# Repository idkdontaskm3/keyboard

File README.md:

# keyboard project!!
### do note - the 75 keyboard is the main project<br>
### the rest is just me learning kicad.
This is just a repo full of my poor attempts at making a keyboard<br>

ive made a very small macro board thingy, alongside a small numpad thing<br>

The 75keyboard pcb is almost complete - I am going to redo some traces<br>
before its done, then start on the case for the keyboard in onshape.<br>

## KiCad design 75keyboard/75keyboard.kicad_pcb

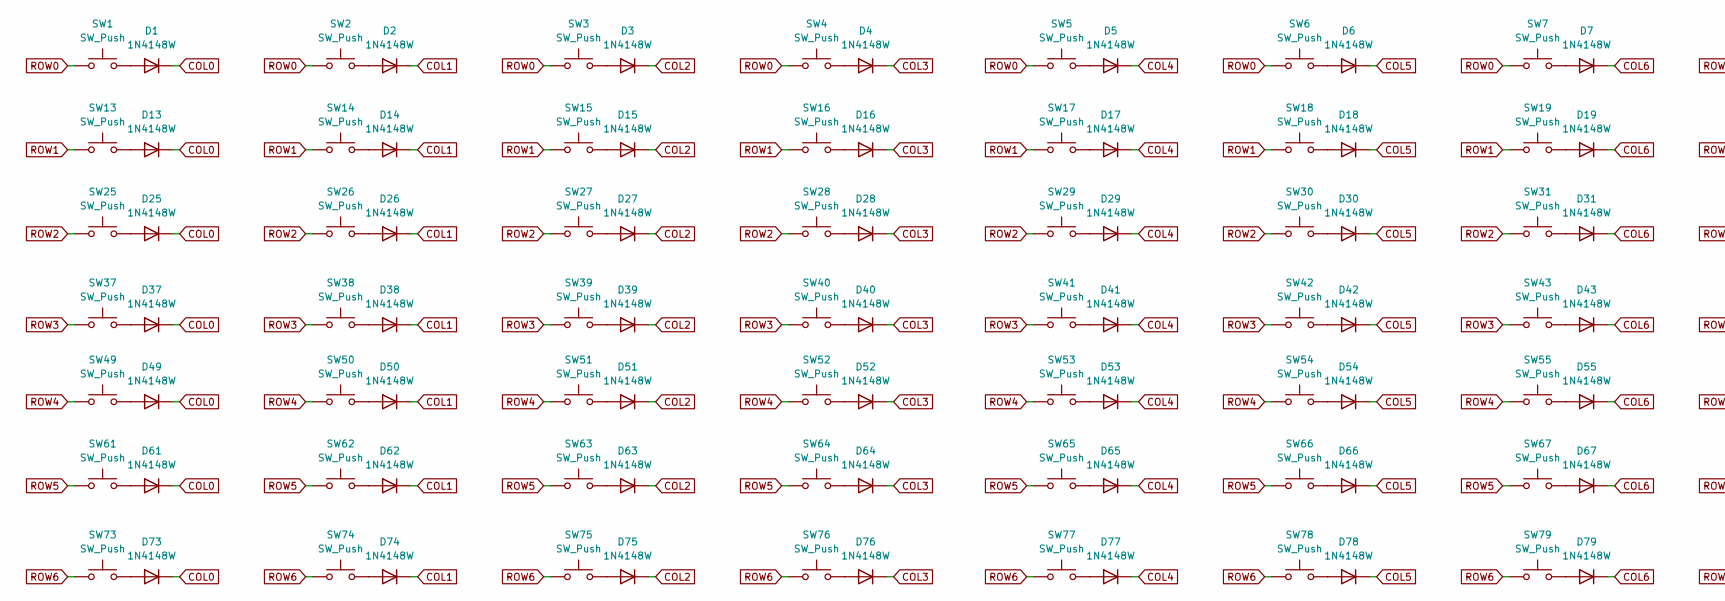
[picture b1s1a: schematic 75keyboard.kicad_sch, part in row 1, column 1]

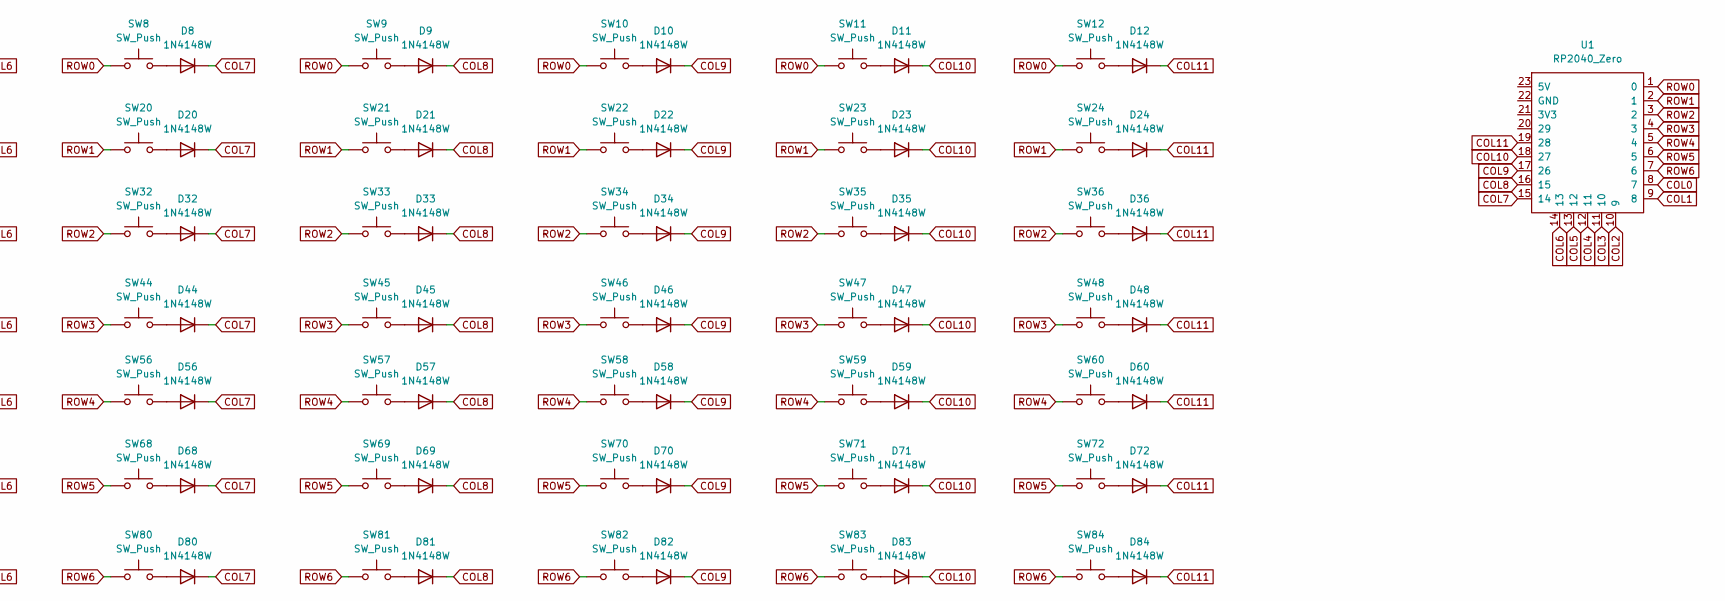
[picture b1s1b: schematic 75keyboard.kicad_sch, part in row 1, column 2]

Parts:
D1, D2, D3, D4, D5, D6, D7, D8, D9, D10, D11, D12, D13, D14, D15, D16, D17, D18, D19, D20, D21, D22, D23, D24, D25, D26, D27, D28, D29, D30, D31, D32, D33, D34, D35, D36, D37, D38, D39, D40, D41, D42, D43, D44, D45, D46, D47, D48, D49, D50, D51, D52, D53, D54, D55, D56, D57, D58, D59, D60, D61, D62, D63, D64, D65, D66, D67, D68, D69, D70, D71, D72, D73, D74, D75, D76, D77, D78, D79, D80, D81, D82, D83, D84: 1N4148W; D_SOD-123
SW1, SW2, SW3, SW4, SW5, SW6, SW7, SW8, SW9, SW10, SW11, SW12, SW13, SW14, SW15, SW16, SW17, SW18, SW19, SW20, SW21, SW22, SW23, SW24, SW25, SW26, SW27, SW28, SW29, SW31, SW33, SW34, SW35, SW36, SW37, SW38, SW39, SW40, SW41, SW42, SW43, SW44, SW46, SW48, SW49, SW50, SW51, SW52, SW53, SW54, SW55, SW56, SW57, SW58, SW60, SW62, SW63, SW64, SW65, SW66, SW67, SW68, SW69, SW70, SW71, SW73, SW74, SW79, SW80, SW81, SW82, SW83, SW84: SW_Push; MX-Solderable-1U
SW30: SW_Push; MX-Solderable-2U
SW32, SW45: SW_Push; MX-Solderable-1.5U
SW47, SW72: SW_Push; MX-Solderable-1.75U
SW59, SW61: SW_Push; MX-Solderable-2.25U
SW75, SW76, SW77: SW_Push; MX-Solderable-1.25U
SW78: SW_Push; MX-Solderable-6.25U
U1: RP2040_Zero

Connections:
COL0: D1.1 (K), D13.1 (K), D25.1 (K), D37.1 (K), D49.1 (K), D61.1 (K), D73.1 (K), U1.8 (7)
COL1: D2.1 (K), D14.1 (K), D26.1 (K), D38.1 (K), D50.1 (K), D62.1 (K), D74.1 (K), U1.9 (8)
COL2: D3.1 (K), D15.1 (K), D27.1 (K), D39.1 (K), D51.1 (K), D63.1 (K), D75.1 (K), U1.10 (9)
COL3: D4.1 (K), D16.1 (K), D28.1 (K), D40.1 (K), D52.1 (K), D64.1 (K), D76.1 (K), U1.11 (10)
COL4: D5.1 (K), D17.1 (K), D29.1 (K), D41.1 (K), D53.1 (K), D65.1 (K), D77.1 (K), U1.12 (11)
COL5: D6.1 (K), D18.1 (K), D30.1 (K), D42.1 (K), D54.1 (K), D66.1 (K), D78.1 (K), U1.13 (12)
COL6: D7.1 (K), D19.1 (K), D31.1 (K), D43.1 (K), D55.1 (K), D67.1 (K), D79.1 (K), U1.14 (13)
COL7: D8.1 (K), D20.1 (K), D32.1 (K), D44.1 (K), D56.1 (K), D68.1 (K), D80.1 (K), U1.15 (14)
COL8: D9.1 (K), D21.1 (K), D33.1 (K), D45.1 (K), D57.1 (K), D69.1 (K), D81.1 (K), U1.16 (15)
COL9: D10.1 (K), D22.1 (K), D34.1 (K), D46.1 (K), D58.1 (K), D70.1 (K), D82.1 (K), U1.17 (26)
COL10: D11.1 (K), D23.1 (K), D35.1 (K), D47.1 (K), D59.1 (K), D71.1 (K), D83.1 (K), U1.18 (27)
COL11: D12.1 (K), D24.1 (K), D36.1 (K), D48.1 (K), D60.1 (K), D72.1 (K), D84.1 (K), U1.19 (28)
unnamed: D1.2 (A), SW1.2
unnamed: D2.2 (A), SW2.2
unnamed: D3.2 (A), SW3.2
unnamed: D4.2 (A), SW4.2
unnamed: D5.2 (A), SW5.2
unnamed: D6.2 (A), SW6.2
unnamed: D7.2 (A), SW7.2
unnamed: D8.2 (A), SW8.2
unnamed: D9.2 (A), SW9.2
unnamed: D10.2 (A), SW10.2
unnamed: D11.2 (A), SW11.2
unnamed: D12.2 (A), SW12.2
unnamed: D13.2 (A), SW13.2
unnamed: D14.2 (A), SW14.2
unnamed: D15.2 (A), SW15.2
unnamed: D16.2 (A), SW16.2
unnamed: D17.2 (A), SW17.2
unnamed: D18.2 (A), SW18.2
unnamed: D19.2 (A), SW19.2
unnamed: D20.2 (A), SW20.2
unnamed: D21.2 (A), SW21.2
unnamed: D22.2 (A), SW22.2
unnamed: D23.2 (A), SW23.2
unnamed: D24.2 (A), SW24.2
unnamed: D25.2 (A), SW25.2
unnamed: D26.2 (A), SW26.2
unnamed: D27.2 (A), SW27.2
unnamed: D28.2 (A), SW28.2
unnamed: D29.2 (A), SW29.2
unnamed: D30.2 (A), SW30.2
unnamed: D31.2 (A), SW31.2
unnamed: D32.2 (A), SW32.2
unnamed: D33.2 (A), SW33.2
unnamed: D34.2 (A), SW34.2
unnamed: D35.2 (A), SW35.2
unnamed: D36.2 (A), SW36.2
unnamed: D37.2 (A), SW37.2
unnamed: D38.2 (A), SW38.2
unnamed: D39.2 (A), SW39.2
unnamed: D40.2 (A), SW40.2
unnamed: D41.2 (A), SW41.2
unnamed: D42.2 (A), SW42.2
unnamed: D43.2 (A), SW43.2
unnamed: D44.2 (A), SW44.2
unnamed: D45.2 (A), SW45.2
unnamed: D46.2 (A), SW46.2
unnamed: D47.2 (A), SW47.2
unnamed: D48.2 (A), SW48.2
unnamed: D49.2 (A), SW49.2
unnamed: D50.2 (A), SW50.2
unnamed: D51.2 (A), SW51.2
unnamed: D52.2 (A), SW52.2
unnamed: D53.2 (A), SW53.2
unnamed: D54.2 (A), SW54.2
unnamed: D55.2 (A), SW55.2
unnamed: D56.2 (A), SW56.2
unnamed: D57.2 (A), SW57.2
unnamed: D58.2 (A), SW58.2
unnamed: D59.2 (A), SW59.2
unnamed: D60.2 (A), SW60.2
unnamed: D61.2 (A), SW61.2
unnamed: D62.2 (A), SW62.2
unnamed: D63.2 (A), SW63.2
unnamed: D64.2 (A), SW64.2
unnamed: D65.2 (A), SW65.2
unnamed: D66.2 (A), SW66.2
unnamed: D67.2 (A), SW67.2
unnamed: D68.2 (A), SW68.2
unnamed: D69.2 (A), SW69.2
unnamed: D70.2 (A), SW70.2
unnamed: D71.2 (A), SW71.2
unnamed: D72.2 (A), SW72.2
unnamed: D73.2 (A), SW73.2
unnamed: D74.2 (A), SW74.2
unnamed: D75.2 (A), SW75.2
unnamed: D76.2 (A), SW76.2
unnamed: D77.2 (A), SW77.2
unnamed: D78.2 (A), SW78.2
unnamed: D79.2 (A), SW79.2
unnamed: D80.2 (A), SW80.2
unnamed: D81.2 (A), SW81.2
unnamed: D82.2 (A), SW82.2
unnamed: D83.2 (A), SW83.2
unnamed: D84.2 (A), SW84.2
ROW0: SW1.1, SW2.1, SW3.1, SW4.1, SW5.1, SW6.1, SW7.1, SW8.1, SW9.1, SW10.1, SW11.1, SW12.1, U1.1 (0)
ROW1: SW13.1, SW14.1, SW15.1, SW16.1, SW17.1, SW18.1, SW19.1, SW20.1, SW21.1, SW22.1, SW23.1, SW24.1, U1.2 (1)
ROW2: SW25.1, SW26.1, SW27.1, SW28.1, SW29.1, SW30.1, SW31.1, SW32.1, SW33.1, SW34.1, SW35.1, SW36.1, U1.3 (2)
ROW3: SW37.1, SW38.1, SW39.1, SW40.1, SW41.1, SW42.1, SW43.1, SW44.1, SW45.1, SW46.1, SW47.1, SW48.1, U1.4 (3)
ROW4: SW49.1, SW50.1, SW51.1, SW52.1, SW53.1, SW54.1, SW55.1, SW56.1, SW57.1, SW58.1, SW59.1, SW60.1, U1.5 (4)
ROW5: SW61.1, SW62.1, SW63.1, SW64.1, SW65.1, SW66.1, SW67.1, SW68.1, SW69.1, SW70.1, SW71.1, SW72.1, U1.6 (5)
ROW6: SW73.1, SW74.1, SW75.1, SW76.1, SW77.1, SW78.1, SW79.1, SW80.1, SW81.1, SW82.1, SW83.1, SW84.1, U1.7 (6)

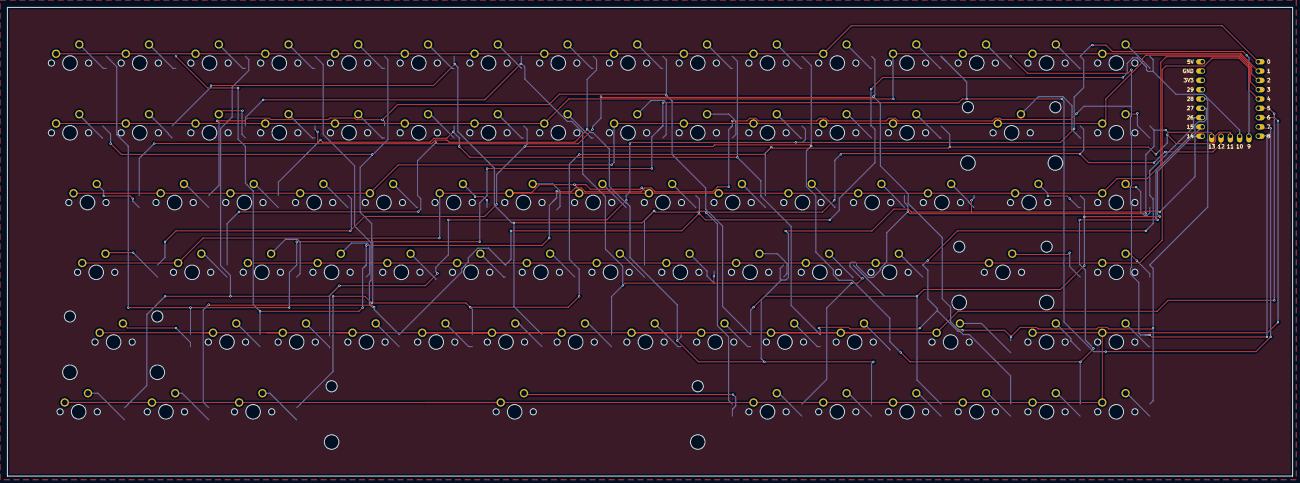
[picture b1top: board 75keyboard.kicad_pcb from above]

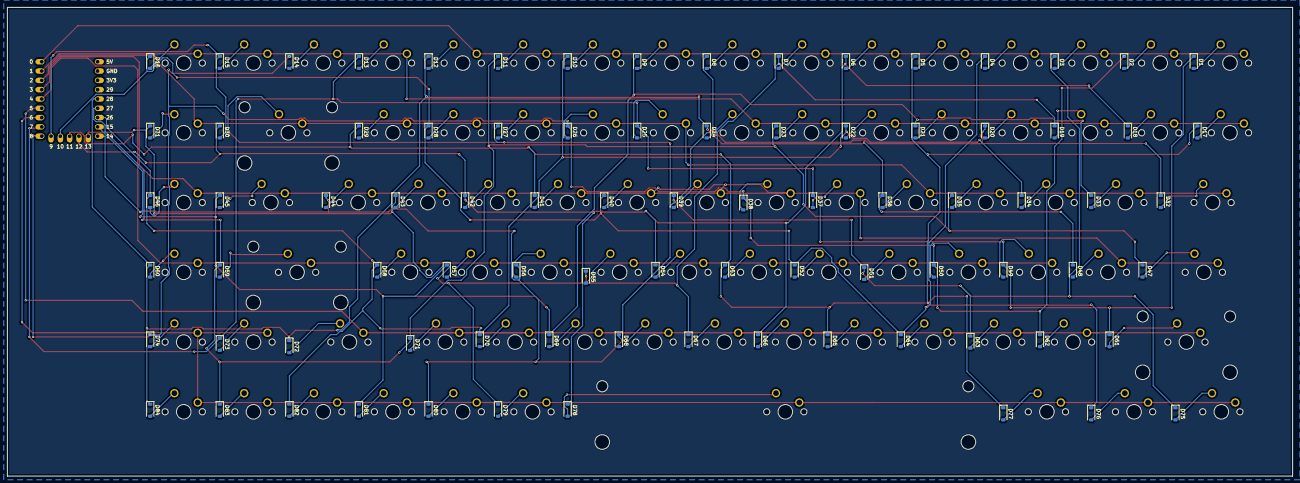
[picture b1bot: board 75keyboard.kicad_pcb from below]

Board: 2 copper layers, 351.0 x 128.0 mm, 169 parts (84 on the bottom side), 103 nets.

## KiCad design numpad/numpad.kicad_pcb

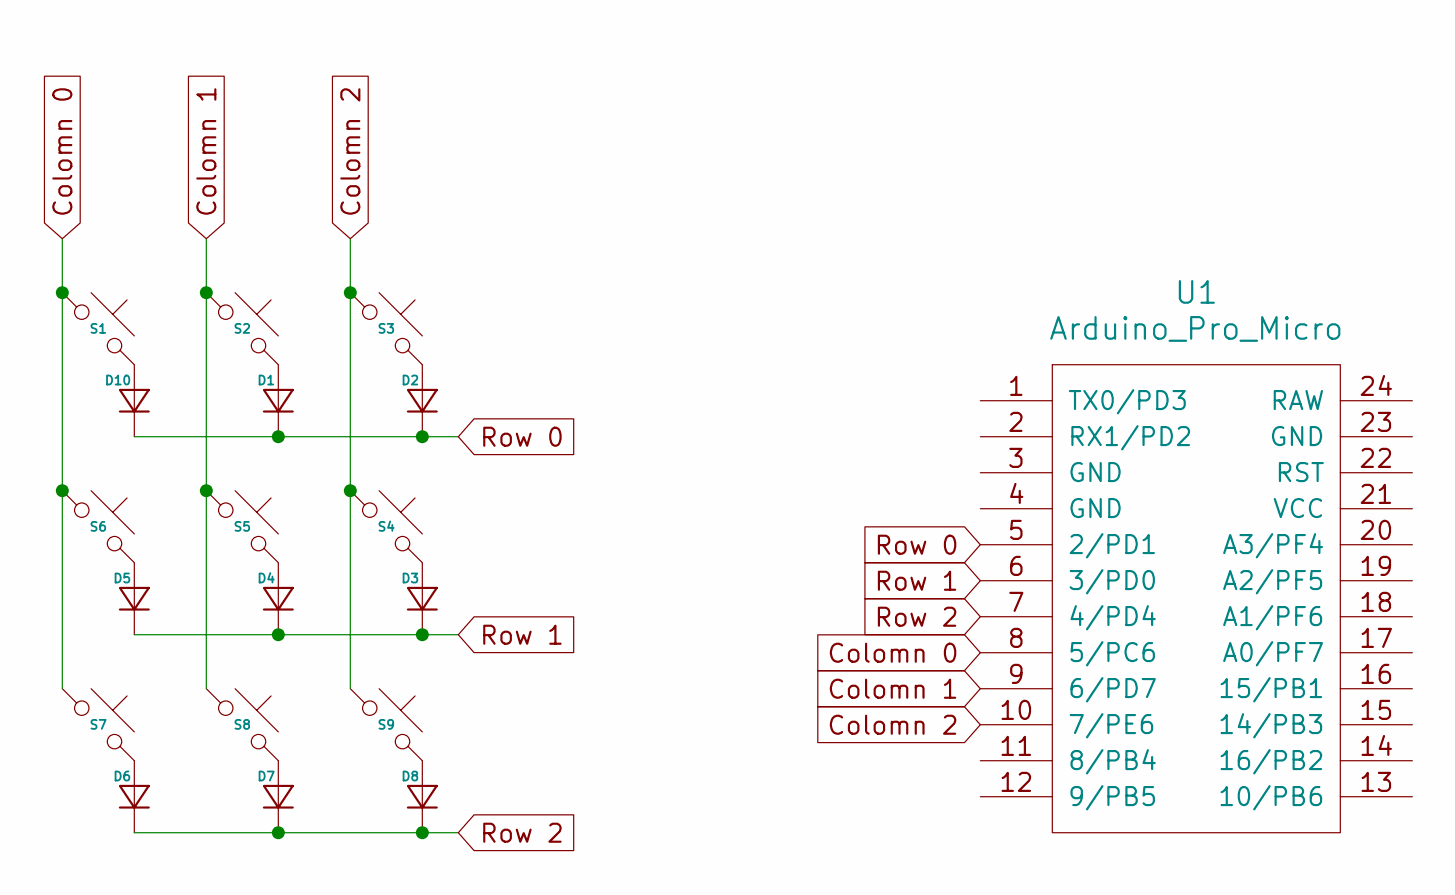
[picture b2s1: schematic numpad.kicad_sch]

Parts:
D1, D2, D3, D4, D5, D6, D7, D8, D10: Diode_DO-35
S1, S2, S3, S4, S5, S6, S7, S8, S9: MX_PCB_1.00u
U1: Arduino_Pro_Micro

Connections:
Colomn 0: S1.1, S6.1, S7.1, U1.8 (5/PC6)
Colomn 1: S2.1, S5.1, S8.1, U1.9 (6/PD7)
Colomn 2: S3.1, S4.1, S9.1, U1.10 (7/PE6)
unnamed: D1.2 (A), S2.2
unnamed: D2.2 (A), S3.2
unnamed: D3.2 (A), S4.2
unnamed: D4.2 (A), S5.2
unnamed: D5.2 (A), S6.2
unnamed: D6.2 (A), S7.2
unnamed: D7.2 (A), S8.2
unnamed: D8.2 (A), S9.2
unnamed: D10.2 (A), S1.2
Row 0: D1.1 (K), D2.1 (K), D10.1 (K), U1.5 (2/PD1)
Row 1: D3.1 (K), D4.1 (K), D5.1 (K), U1.6 (3/PD0)
Row 2: D6.1 (K), D7.1 (K), D8.1 (K), U1.7 (4/PD4)

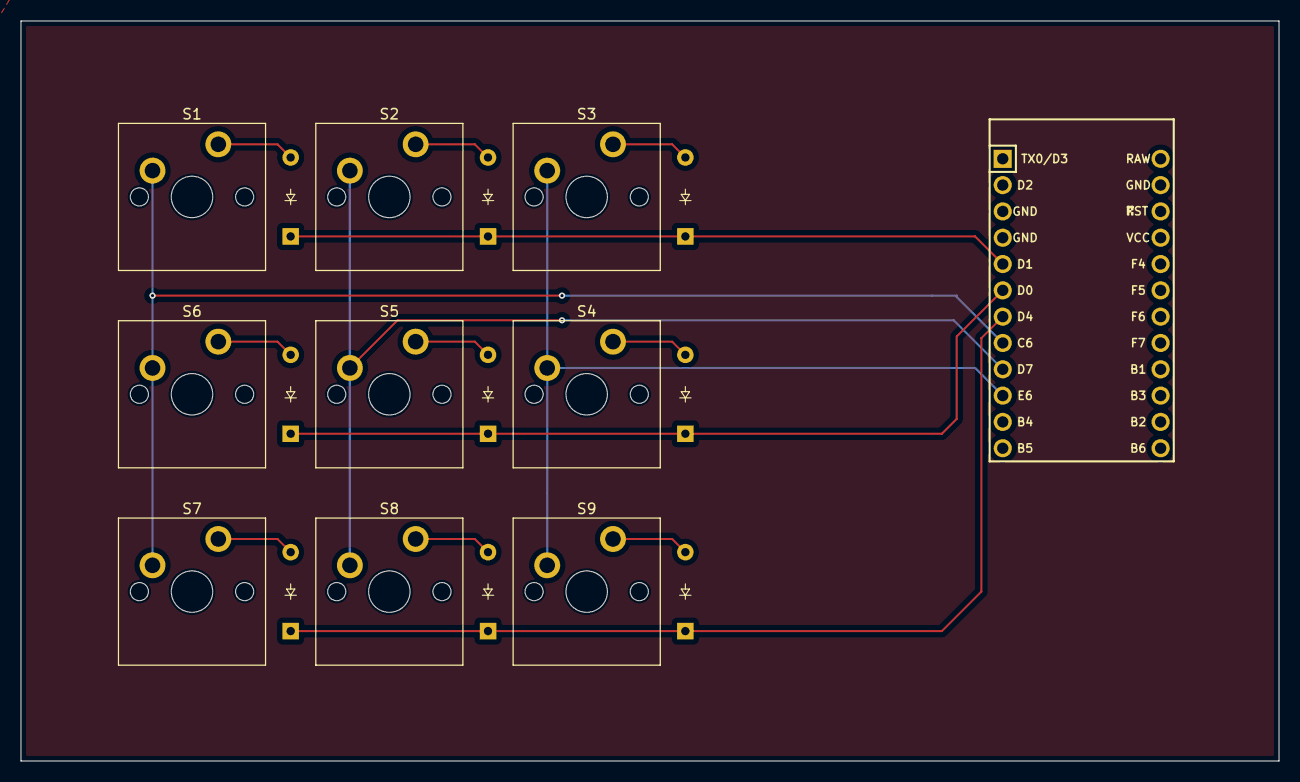
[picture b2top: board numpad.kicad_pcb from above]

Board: 2 copper layers, 121.4 x 71.4 mm, 19 parts (0 on the bottom side), 15 nets.

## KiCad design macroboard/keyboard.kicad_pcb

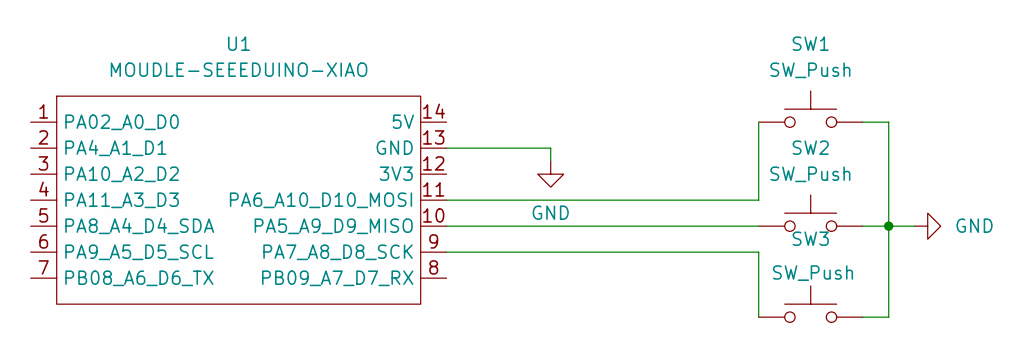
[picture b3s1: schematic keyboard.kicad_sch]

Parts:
SW1, SW2, SW3: SW_Push; SW_Cherry_MX_1.00u_PCB
U1: MOUDLE-SEEEDUINO-XIAO; XIAO-Generic-Hybrid-14P-2.54-21X17.8MM

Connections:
GND: SW1.2, SW2.2, SW3.2, U1.13 (GND)
unnamed: SW2.1, U1.10 (PA5_A9_D9_MISO)
unnamed: SW1.1, U1.11 (PA6_A10_D10_MOSI)
unnamed: SW3.1, U1.9 (PA7_A8_D8_SCK)

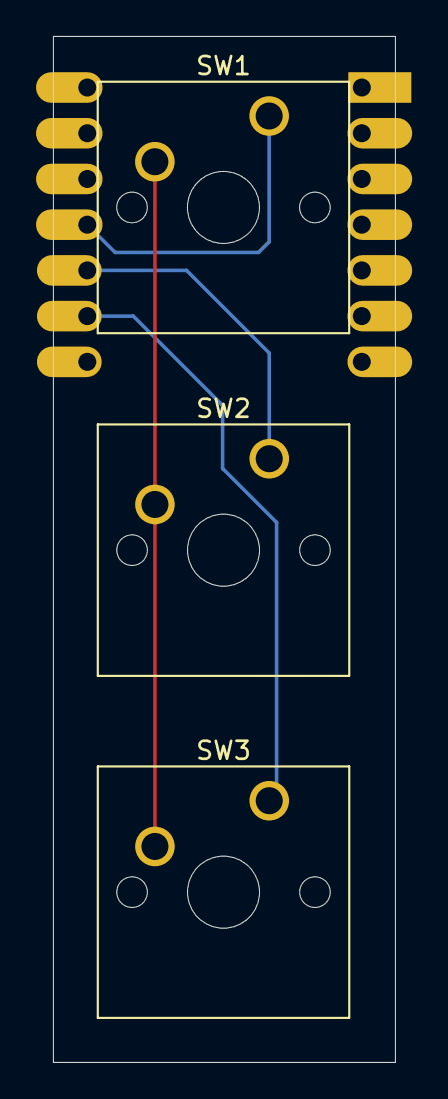
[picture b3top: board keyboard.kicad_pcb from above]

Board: 2 copper layers, 19.0 x 57.0 mm, 4 parts (1 on the bottom side), 4 nets.

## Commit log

2026-03-01 .\README.md
